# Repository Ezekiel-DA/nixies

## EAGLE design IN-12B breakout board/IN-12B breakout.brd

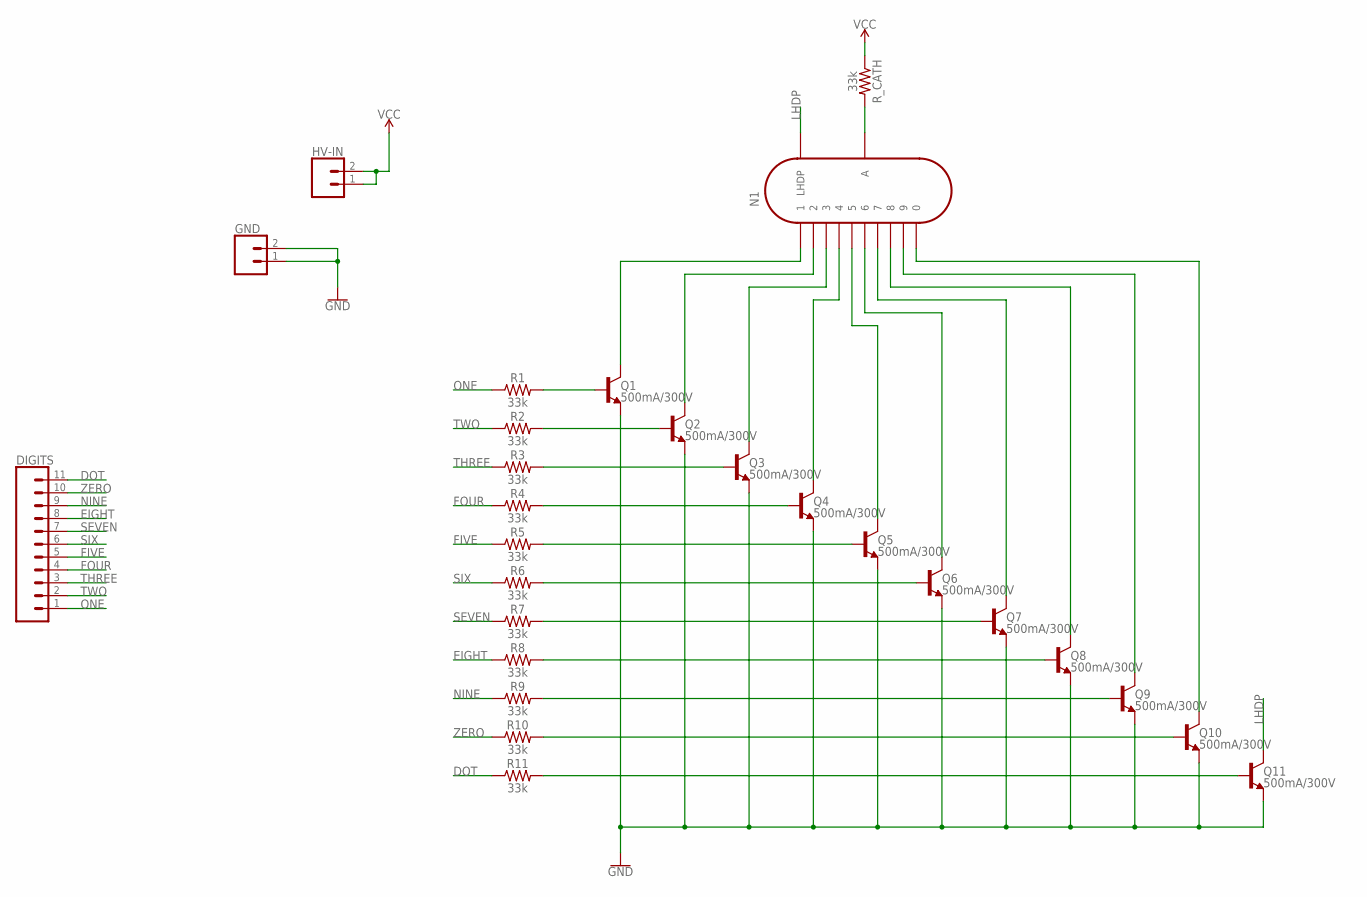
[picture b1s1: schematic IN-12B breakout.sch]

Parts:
DIGITS: CONN_11; 1X11
GND: CONN_02; 1X02
HV-IN: CONN_02; 1X02
N1: IN-12B; IN-12
Q1, Q2, Q3, Q4, Q5, Q6, Q7, Q8, Q9, Q10, Q11: 500mA/300V; SOT23-3
R1, R2, R3, R4, R5, R6, R7, R8, R9, R10, R11: 33k; 0603
R_CATH: 33k; 0603

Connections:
DOT: DIGITS.11, R11.1
EIGHT: DIGITS.8, R8.1
FIVE: DIGITS.5, R5.1
FOUR: DIGITS.4, R4.1
GND: GND.1, GND.2, Q1.2 (E), Q2.2 (E), Q3.2 (E), Q4.2 (E), Q5.2 (E), Q6.2 (E), Q7.2 (E), Q8.2 (E), Q9.2 (E), Q10.2 (E), Q11.2 (E)
LHDP: N1.LHDP, Q11.3 (C)
unnamed: Q1.1 (B), R1.2
unnamed: Q2.1 (B), R2.2
unnamed: Q3.1 (B), R3.2
unnamed: Q4.1 (B), R4.2
unnamed: Q5.1 (B), R5.2
unnamed: Q6.1 (B), R6.2
unnamed: Q7.1 (B), R7.2
unnamed: Q8.1 (B), R8.2
unnamed: Q9.1 (B), R9.2
unnamed: Q10.1 (B), R10.2
unnamed: N1.1, Q1.3 (C)
unnamed: N1.2, Q2.3 (C)
unnamed: N1.3, Q3.3 (C)
unnamed: N1.4, Q4.3 (C)
unnamed: N1.5, Q5.3 (C)
unnamed: N1.6, Q6.3 (C)
unnamed: N1.7, Q7.3 (C)
unnamed: N1.8, Q8.3 (C)
unnamed: N1.9, Q9.3 (C)
unnamed: N1.0, Q10.3 (C)
unnamed: N1.A, R_CATH.2
unnamed: Q11.1 (B), R11.2
NINE: DIGITS.9, R9.1
ONE: DIGITS.1, R1.1
SEVEN: DIGITS.7, R7.1
SIX: DIGITS.6, R6.1
THREE: DIGITS.3, R3.1
TWO: DIGITS.2, R2.1
VCC: HV-IN.1, HV-IN.2, R_CATH.1
ZERO: DIGITS.10, R10.1

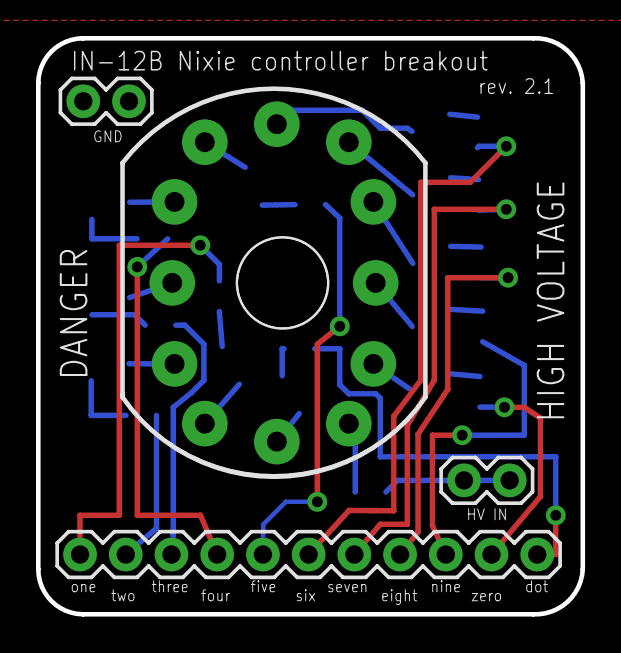
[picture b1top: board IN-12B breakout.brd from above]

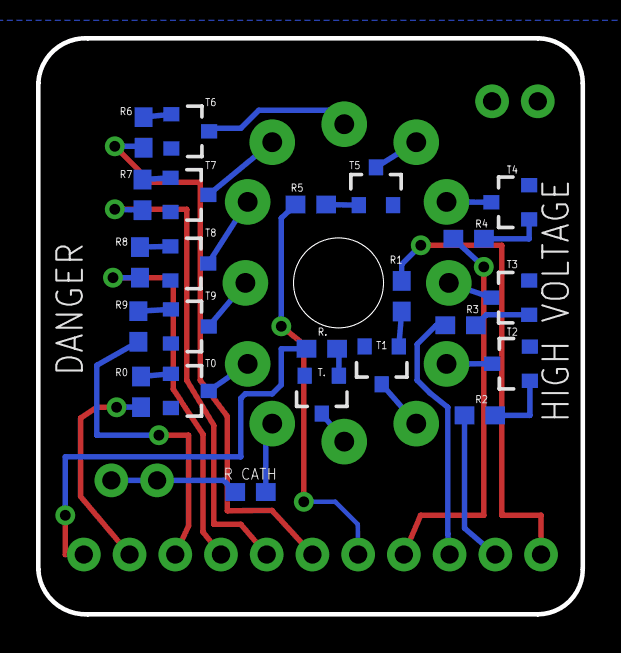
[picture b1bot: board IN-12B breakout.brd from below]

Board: 2 copper layers, 30.2 x 32.0 mm, 27 parts (23 on the bottom side), 36 nets.

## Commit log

2017-01-15 board version 2.0, with decimal dot support
2017-01-16 BOM, CAD model
2017-01-16 all components expect Rs done
2017-01-17 basic laser cut frame
2017-01-19 ordered components

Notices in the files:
parts and their libraries:
SparkFun-DiscreteSemi: Licensing: Creative Commons ShareAlike 4.0 International - https://creativecommons.org/licenses/by-sa/4.0
